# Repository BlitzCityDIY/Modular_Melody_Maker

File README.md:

# Modular_Melody_Maker
 Files for the Modular Melody Maker project. Currently a work in progress.

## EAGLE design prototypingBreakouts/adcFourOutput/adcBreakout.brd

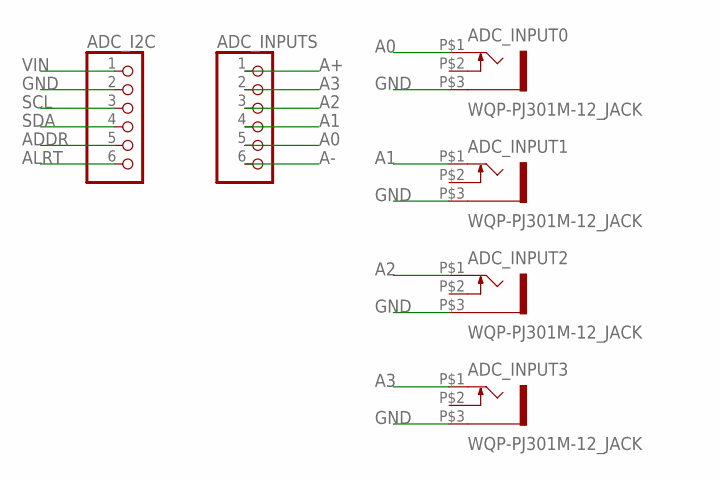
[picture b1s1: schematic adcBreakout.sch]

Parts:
ADC_I2C: PINHD-1X6B; 1X06-BIG
ADC_INPUT0, ADC_INPUT1, ADC_INPUT2, ADC_INPUT3: WQP-PJ301M-12_JACK
ADC_INPUTS: PINHD-1X6B; 1X06-BIG

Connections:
A0: ADC_INPUT0.P$1 (2), ADC_INPUTS.5
A1: ADC_INPUT1.P$1 (2), ADC_INPUTS.4
A2: ADC_INPUT2.P$1 (2), ADC_INPUTS.3
A3: ADC_INPUT3.P$1 (2), ADC_INPUTS.2
A+: ADC_INPUTS.1
A-: ADC_INPUTS.6
ADDR: ADC_I2C.5
ALRT: ADC_I2C.6
GND: ADC_I2C.2, ADC_INPUT0.P$3 (1), ADC_INPUT1.P$3 (1), ADC_INPUT2.P$3 (1), ADC_INPUT3.P$3 (1)
SCL: ADC_I2C.3
SDA: ADC_I2C.4
VIN: ADC_I2C.1

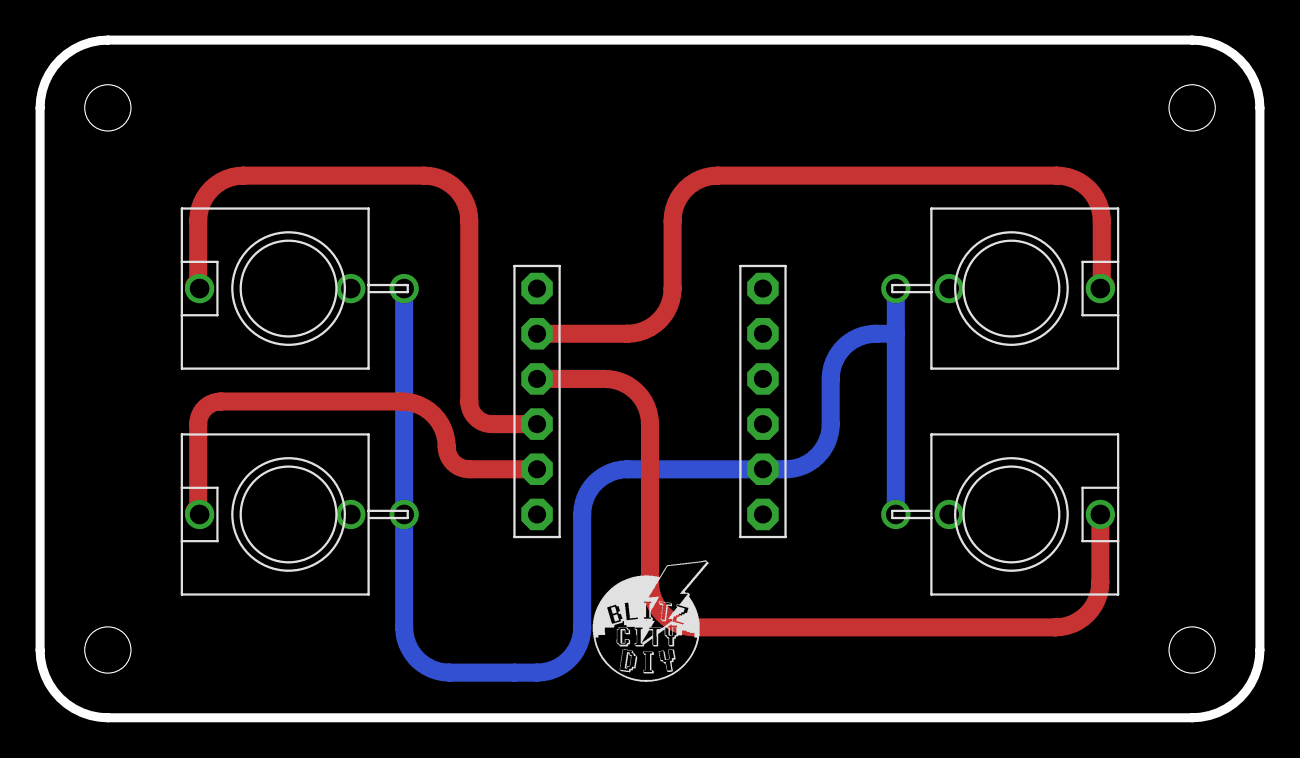
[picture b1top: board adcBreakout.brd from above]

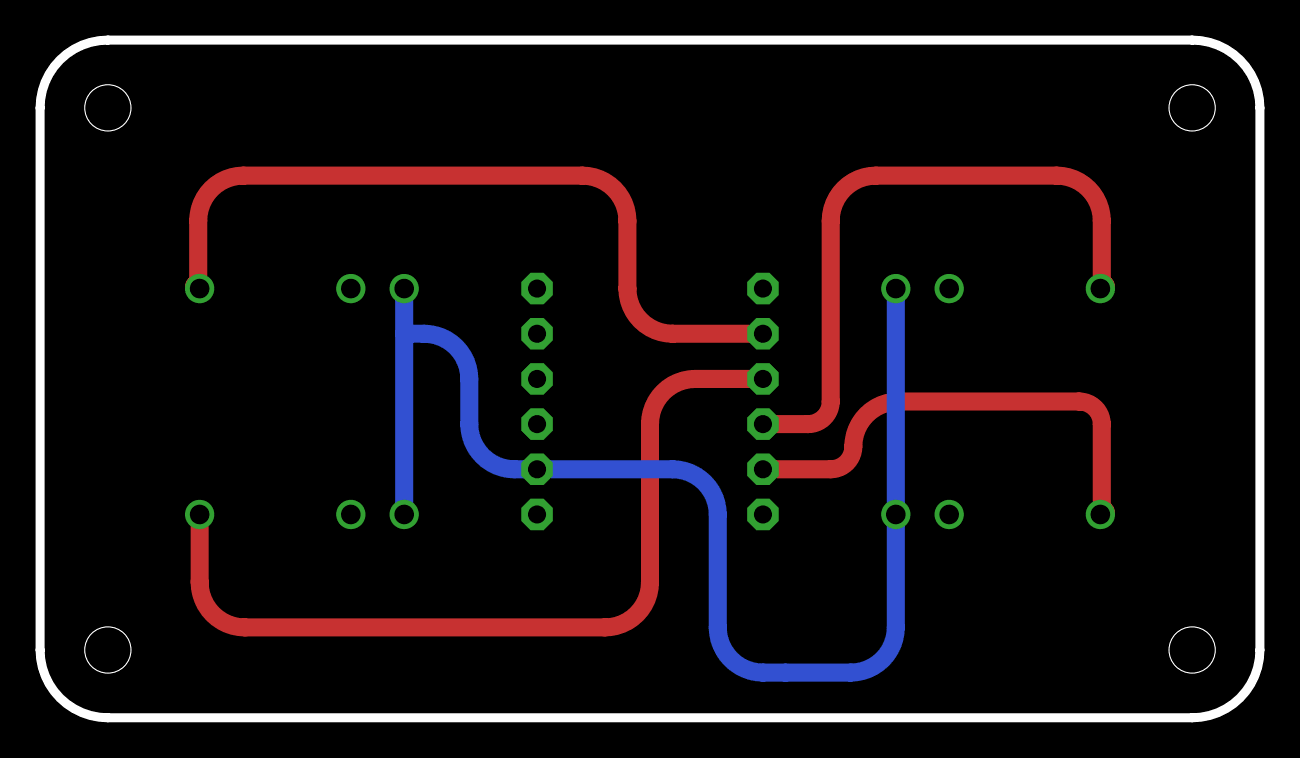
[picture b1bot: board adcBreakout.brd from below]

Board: 2 copper layers, 68.6 x 38.1 mm, 15 parts (2 on the bottom side), 5 nets.

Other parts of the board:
PLABEL0: PLABEL0
PLABEL1: PLABEL1
PLABEL2: PLABEL2
PLABEL3: PLABEL3
PLABEL4: PLABEL4
PLABEL5: PLABEL5
PLABEL6: PLABEL6
PLABEL7: PLABEL7
PLABEL8: PLABEL8

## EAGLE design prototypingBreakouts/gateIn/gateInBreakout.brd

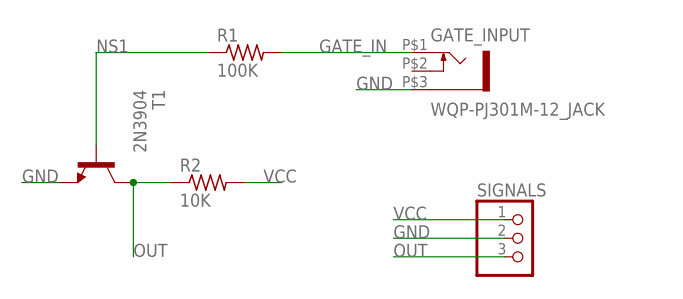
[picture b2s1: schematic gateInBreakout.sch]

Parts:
GATE_INPUT: WQP-PJ301M-12_JACK
R1: 100K; 0207/9
R2: 10K; 0207/9
SIGNALS: PINHD-1X3; 1X03
T1: 2N3904; TO92

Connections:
GATE_IN: GATE_INPUT.P$1 (2), R1.2
GND: GATE_INPUT.P$3 (1), SIGNALS.2, T1.3 (E)
NS1: R1.1, T1.2 (B)
OUT: R2.1, SIGNALS.3, T1.1 (C)
VCC: R2.2, SIGNALS.1

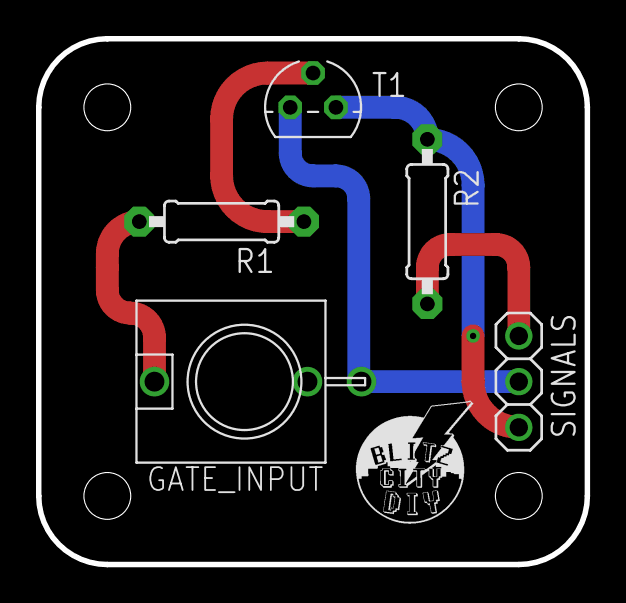
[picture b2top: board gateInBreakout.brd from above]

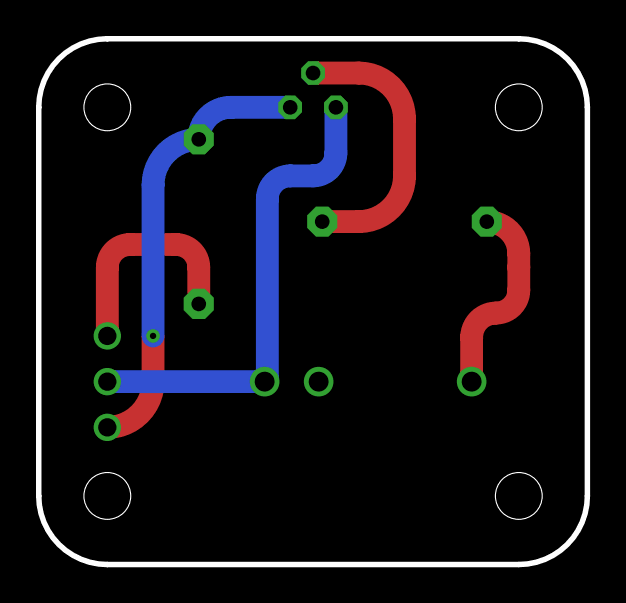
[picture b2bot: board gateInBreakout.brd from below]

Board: 2 copper layers, 30.5 x 29.2 mm, 13 parts (2 on the bottom side), 5 nets.

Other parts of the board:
BLABEL0: BLABEL0
BLABEL1: BLABEL1
PLABEL0: PLABEL0
PLABEL1: PLABEL1
PLABEL2: PLABEL2
PLABEL3: PLABEL3
PLABEL4: PLABEL4
PLABEL5: PLABEL5

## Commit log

2022-12-11 Adding v0 of the code and volts
    Adding v0 of the code, 1 input 1 output. volts.py is a helper file for 1v/oct
2022-12-11 adding 2 in/2 out
2022-12-22 draft 4in/4out
2022-12-22 updating file/folder names
2022-12-22 updating file names
2023-01-13 Adding breakout PCB files
    Adding breakout PCB files *UNTESTED*
